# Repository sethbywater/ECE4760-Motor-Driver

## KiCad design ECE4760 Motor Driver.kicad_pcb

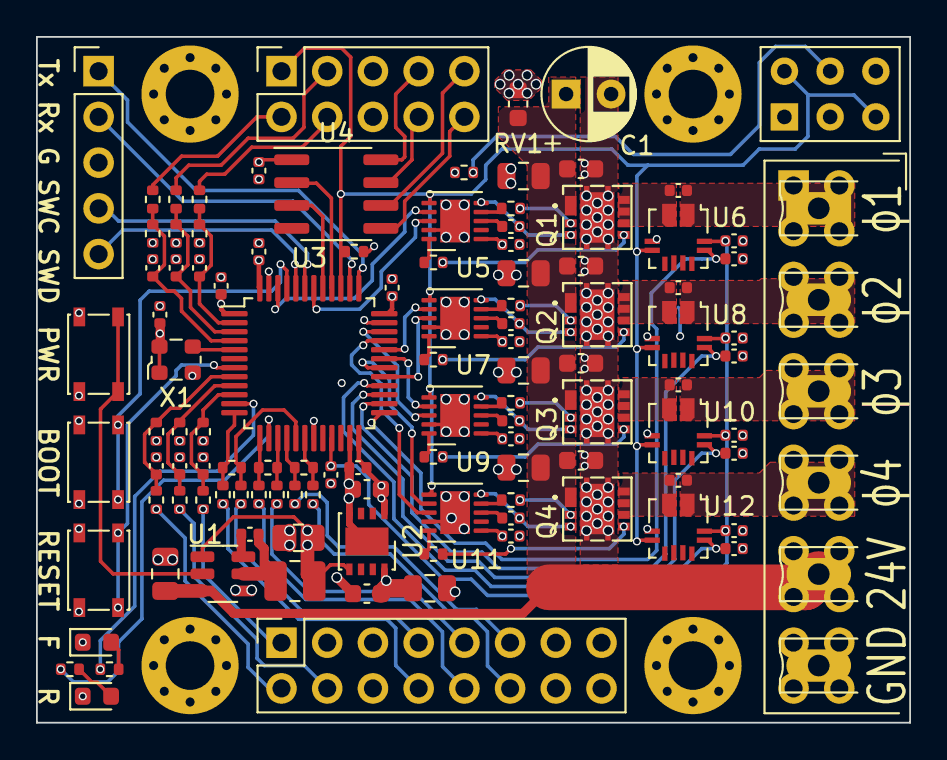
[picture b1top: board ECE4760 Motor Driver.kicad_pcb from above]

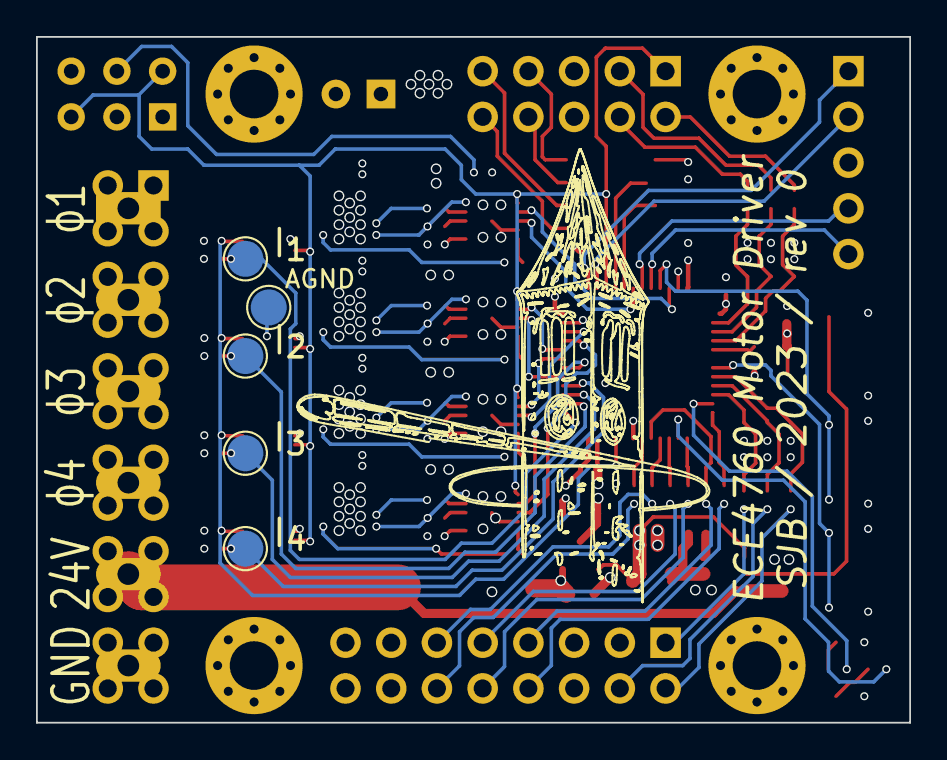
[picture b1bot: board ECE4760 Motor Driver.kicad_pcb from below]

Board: 6 copper layers, 48.5 x 38.1 mm, 120 parts (6 on the bottom side), 94 nets.

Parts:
C1: 22u 100V; CP_Radial_D5.0mm_P2.50mm
C2, C3, C4, C5, C6, C7, C8, C14, C15, C18, C20, C22, C25, C27, C29, C32, C34, C36, C39, C41, C46, C47, C48: 100n; C_0402_1005Metric
C9: 4u7, 50V; C_0805_2012Metric
C10, C11: 22u; C_0805_2012Metric
C12, C13: 4u7; C_0603_1608Metric
C16, C23, C30, C37: 100n, 50V, 0603, X7R; C_0603_1608Metric
C17, C24, C31, C38: 4u7, 50V, 0805, X7R; C_0805_2012Metric
C19, C26, C33, C40: C; C_0402_1005Metric
C21, C28, C35, C42, C43, C44, C45: 1n; C_0402_1005Metric
D1, D2: Green; LED_0603_1608Metric
H1, H2, H3, H4: MountingHole_Pad; MountingHole_2.7mm_M2.5_Pad_Via
J1: Comms; PinHeader_1x05_P2.54mm_Vertical
J2: IO; PinSocket_2x05_P2.54mm_Vertical
J3: IO; PinSocket_2x08_P2.54mm_Vertical
J4: Alternative Motor; PinSocket_2x12_P2.54mm_Vertical
J5: Motor / Power; PhoenixContact_MCV_1,5_6-G-5.08_1x06_P5.08mm_Vertical
L1: 4u7; L_1008_2520Metric
Q1, Q2, Q3, Q4: CSD87333Q3D
R1, R3, R4: 330R; R_0402_1005Metric
R2, R13, R15, R17, R28, R30, R32: 4k7; R_0402_1005Metric
R5, R6, R7, R8, R9, R10, R11, R12: 4R7; R_0402_1005Metric
R14, R16, R18, R29, R31, R33: 100; R_0402_1005Metric
R19, R20, R21, R22, R23, R24, R25, R26, R27: 1k, 1%; R_0402_1005Metric
RV1: 26V 200A; C_0603_1608Metric
SW1: RESET; SW_SPST_PTS810
SW2: BOOT; SW_SPST_PTS810
SW3: POWER; SW_SPST_PTS810
SW4: G12JPC; SW_NKK_G1xJP
TP1, TP2, TP3, TP4, TP5: Sense; TestPoint_Pad_D2.0mm
U1: AP63205WU; TSOT-23-6
U2: AP7361C-33FGE; DFN-8-1EP_3x3mm_P0.65mm_EP1.55x2.4mm
U3: STM32G473CETx; LQFP-48_7x7mm_P0.5mm
U4: THVD1451D; SOIC-8_3.9x4.9mm_P1.27mm
U5, U7, U9, U11: DGD05473FNQ; DFN-10-1EP_3x3mm_P0.5mm_EP1.65x2.38mm
U6, U8, U10, U12: ACS711xEXLT-15AB; Allegro_QFN-12-10-1EP_3x3mm_P0.5mm
X1: 48MHz; Oscillator_SMD_ECS_2520MV-xxx-xx-4Pin_2.5x2.0mm

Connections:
+3V3: C2.2, C3.1, C4.1, C5.1, C6.1, C7.1, C13.1, C14.1, C20.2, C27.2, C34.2, C41.2, U2.1 (OUT), U3.1 (VBAT), U3.21 (VDDA), U3.24 (VDD), U3.36 (VDD), U3.48 (VDD), U4.1 (VCC), U6.10 (VCC), U8.10 (VCC), U10.10 (VCC), U12.10 (VCC), X1.1 (Tri-State), X1.4 (VDD)
+5V: C10.1, C11.1, C12.1, C15.1, C22.1, C29.1, C36.1, J2.5, J3.3, J3.5, J3.13, J3.15, L1.2, R1.2, R2.1, R13.1, R15.1, R17.1, R28.1, R30.1, R32.1, U1.1 (FB), U2.5 (EN), U2.8 (IN), U5.1 (VCC), U7.1 (VCC), U9.1 (VCC), U11.1 (VCC)
/BOOT: SW2.2, U3.45 (PB8)
/CLK: U3.40 (SPI1_SCK), U4.2 (R)
/DATA: U3.41 (SPI1_MISO), U4.3 (D)
/ENC_A+: R22.2, R23.2, U3.15 (COMP2_INP)
/ENC_A-: R23.1, R24.2, U3.13 (COMP2_INM)
/ENC_B+: R25.2, R26.2, U3.16 (COMP4_INP)
/ENC_B-: R26.1, R27.2, U3.18 (COMP4_INM)
/ENC_I+: R19.2, R20.2, U3.17 (COMP1_INP)
/ENC_I-: R20.1, R21.2, U3.12 (COMP1_INM)
/HALL_A: C45.1, R17.2, R18.2, U3.8 (TIM2_CH1)
/HALL_B: C43.1, R13.2, R14.2, U3.9 (TIM2_CH2)
/HALL_C: C44.1, R15.2, R16.2, U3.10 (TIM2_CH3)
/LED_1: R3.1, U3.11 (PA3)
/LED_2: R4.1, U3.14 (PA6)
/LIM_H: C48.1, R32.2, R33.2, U3.4 (PC15)
/LIM_L: C46.1, R28.2, R29.2, U3.2 (PC13)
/LIM_R: C47.1, R30.2, R31.2, U3.3 (PC14)
/OSC_IN: U3.5 (RCC_OSC_IN), X1.3 (OUT)
/PH1_HI: U3.46 (TIM8_CH3), U5.7 (HIN)
/PH1_LO: U3.42 (TIM8_CH3N), U5.8 (LIN)
/PH1_SENSE: C21.2, TP2.1, U3.25 (OPAMP4_VINP), U6.9 (VIOUT)
/PH2_HI: U3.32 (TIM1_CH3), U7.7 (HIN)
/PH2_LO: U3.29 (TIM1_CH3N), U7.8 (LIN)
/PH2_SENSE: C28.2, TP3.1, U3.26 (OPAMP6_VINP), U8.9 (VIOUT)
/PH3_HI: U3.31 (TIM1_CH2), U9.7 (HIN)
/PH3_LO: U3.34 (TIM1_CH2N), U9.8 (LIN)
/PH3_SENSE: C35.2, TP4.1, U3.27 (OPAMP3_VINP), U10.9 (VIOUT)
/PH4_HI: U3.30 (TIM1_CH1), U11.7 (HIN)
/PH4_LO: U3.33 (TIM1_CH1N), U11.8 (LIN)
/PH4_SENSE: C42.2, TP5.1, U3.28 (OPAMP2_VINP), U12.9 (VIOUT)
/SWCLK: J1.2, U3.38 (SYS_JTCK-SWCLK)
/SWDIO: J1.1, U3.37 (SYS_JTMS-SWDIO)
/UART_RX: J1.5, U3.44 (USART1_RX)
/UART_TX: J1.4, U3.43 (USART1_TX)
/~RST: SW1.2, U3.7 (RCC_MCO)
CLK+: J2.7, U4.8 (A)
CLK-: J2.8, U4.7 (B)
DATA+: J2.10, U4.5 (Y)
DATA-: J2.9, U4.6 (Z)
Enc_A_In+: J3.9, R22.1
Enc_A_In-: J3.10, R24.1
Enc_B_In+: J3.11, R25.1
Enc_B_In-: J3.12, R27.1
Enc_I_In+: J3.7, R19.1
Enc_I_In-: J3.8, R21.1
Fault_Enable: J2.1, R2.2, SW4.3, SW4.6 (K), U3.39 (PA15), U5.6 (EN), U6.4 (~FAULT), U7.6 (EN), U8.4 (~FAULT), U9.6 (EN), U10.4 (~FAULT), U11.6 (EN), U12.4 (~FAULT)
GND: C1.2, C2.1, C3.2, C4.2, C5.2, C6.2, C7.2, C9.2, C10.2, C11.2, C12.2, C13.2, C14.2, C15.2, C16.2, C17.2, C20.1, C21.1, C22.2, C23.2, C24.2, C27.1, C28.1, C29.2, C30.2, C31.2, C34.1, C35.1, C36.2, C37.2, C38.2, C41.1, C42.1, C43.2, C44.2, C45.2, C46.2, C47.2, C48.2, D1.1 (K), D2.1 (K), H1.1, H2.1, H3.1, H4.1, J1.3, J2.6, J3.6, J3.14, J3.16, J4.21, J4.22, J4.23, J4.24, J5.6, Q1.9 (GND), Q1.10 (GND), Q1.11 (GND), Q1.12 (GND), Q1.13 (GND), Q2.9 (GND), Q2.10 (GND), Q2.11 (GND), Q2.12 (GND), Q2.13 (GND), Q3.9 (GND), Q3.10 (GND), Q3.11 (GND), Q3.12 (GND), Q3.13 (GND), Q4.9 (GND), Q4.10 (GND), Q4.11 (GND), Q4.12 (GND), Q4.13 (GND), RV1.2, SW1.1, SW2.1, SW3.1, SW4.2 (COM), TP1.1, U1.4 (GND), U2.4 (GND), U2.9 (GND), U3.19 (VSSA), U3.23 (VSS), U3.35 (VSS), U3.47 (VSS), U4.4 (GND), U5.9 (COM), U5.11 (EP), U6.3 (GND), U7.9 (COM), U7.11 (EP), U8.3 (GND), U9.9 (COM), U9.11 (EP), U10.3 (GND), U11.9 (COM), U11.11 (EP), U12.3 (GND), X1.2 (GND)
Hall_A_In: J3.2, R18.1
Hall_B_In: J3.4, R14.1
Hall_C_In: J3.1, R16.1
Lim_H_In: J2.2, R33.1
Lim_L_In: J2.4, R29.1
Lim_R_In: J2.3, R31.1
unnamed: D1.2 (A), R4.2
unnamed: D2.2 (A), R3.2
unnamed: Q1.5 (BG), R6.2
unnamed: Q1.3 (TG), R5.1
unnamed: C18.2, Q1.4 (TGR), U5.5 (VS)
unnamed: Q2.5 (BG), R8.2
unnamed: Q2.3 (TG), R7.1
unnamed: C25.2, Q2.4 (TGR), U7.5 (VS)
unnamed: Q3.5 (BG), R10.2
unnamed: Q3.3 (TG), R9.1
unnamed: C32.2, Q3.4 (TGR), U9.5 (VS)
unnamed: Q4.5 (BG), R12.2
unnamed: Q4.3 (TG), R11.1
unnamed: C39.2, Q4.4 (TGR), U11.5 (VS)
unnamed: R1.1, SW4.5 (A)
unnamed: C8.1, U1.6 (BST)
unnamed: SW3.2, U1.2 (EN)
unnamed: C8.2, L1.1, U1.5 (SW)
unnamed: R5.2, U5.4 (HO)
unnamed: R6.1, U5.10 (LO)
unnamed: C18.1, U5.3 (VB)
unnamed: C19.1, Q1.6 (SW), Q1.7 (SW), Q1.8 (SW), U6.2 (IP-)
unnamed: R7.2, U7.4 (HO)
unnamed: R8.1, U7.10 (LO)
unnamed: C25.1, U7.3 (VB)
unnamed: C26.1, Q2.6 (SW), Q2.7 (SW), Q2.8 (SW), U8.2 (IP-)
unnamed: R9.2, U9.4 (HO)
unnamed: R10.1, U9.10 (LO)
unnamed: C32.1, U9.3 (VB)
unnamed: C33.1, Q3.6 (SW), Q3.7 (SW), Q3.8 (SW), U10.2 (IP-)
unnamed: R11.2, U11.4 (HO)
unnamed: R12.1, U11.10 (LO)
unnamed: C39.1, U11.3 (VB)
unnamed: C40.1, Q4.6 (SW), Q4.7 (SW), Q4.8 (SW), U12.2 (IP-)
PH1: C19.2, J4.1, J4.2, J4.3, J4.4, J5.1, U6.1 (IP+)
PH2: C26.2, J4.5, J4.6, J4.7, J4.8, J5.2, U8.1 (IP+)
PH3: C33.2, J4.9, J4.10, J4.11, J4.12, J5.3, U10.1 (IP+)
PH4: C40.2, J4.13, J4.14, J4.15, J4.16, J5.4, U12.1 (IP+)
Vdrive: C1.1, C9.1, C16.1, C17.1, C23.1, C24.1, C30.1, C31.1, C37.1, C38.1, J4.17, J4.18, J4.19, J4.20, J5.5, Q1.1 (VIN), Q2.1 (VIN), Q3.1 (VIN), Q4.1 (VIN), RV1.1, U1.3 (IN)

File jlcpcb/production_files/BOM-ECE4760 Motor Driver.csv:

Comment,Designator,Footprint,LCSC
4k7,"R13,R15,R17,R2,R28,R30,R32",R_0402_1005Metric,C105870
330R,"R1,R3,R4",R_0402_1005Metric,C105875
100,"R14,R16,R18,R29,R31,R33",R_0402_1005Metric,C106233
Green,"D1,D2",LED_0603_1608Metric,C125101
4R7,"R10,R11,R12,R5,R6,R7,R8,R9",R_0402_1005Metric,C137862
ACS711xEXLT-15AB,"U10,U12,U6,U8",Allegro_QFN-12-10-1EP_3x3mm_P0.5mm,C150824
AP7361C-33FGE,U2,DFN-8-1EP_3x3mm_P0.65mm_EP1.55x2.4mm,C151007
"100n, 50V, 0603, X7R","C16,C23,C30,C37",C_0603_1608Metric,C161117
AP63205WU,U1,TSOT-23-6,C2071056
RESET,"SW1,SW2,SW3",SW_SPST_PTS810,C221896
"1k, 1%","R19,R20,R21,R22,R23,R24,R25,R26,R27",R_0402_1005Metric,C242161
26V 200A,RV1,C_0603_1608Metric,C2655584
THVD1451D,U4,SOIC-8_3.9x4.9mm_P1.27mm,C2671319
DGD05473FNQ,"U11,U5,U7,U9",DFN-10-1EP_3x3mm_P0.5mm_EP1.65x2.38mm,C2677131
1n,"C21,C28,C35,C42,C43,C44,C45",C_0402_1005Metric,C277522
48MHz,X1,Oscillator_SMD_ECS_2520MV-xxx-xx-4Pin_2.5x2.0mm,C390534
4u7,"C12,C13,C17,C24,C31,C38,C9",C_0603_1608Metric,C437557
100n,"C14,C15,C18,C2,C20,C22,C25,C27,C29,C3,C32,C34,C36,C39,C4,C41,C46,C47,C48,C5,C6,C7,C8",C_0402_1005Metric,C71629
STM32G473CETx,U3,LQFP-48_7x7mm_P0.5mm,C730111
4u7,L1,L_1008_2520Metric,C82314
22u,"C10,C11",C_0805_2012Metric,C86816
CSD87333Q3D,"Q1,Q2,Q3,Q4",CSD87333Q3D,C90396
IO,J2,PinSocket_2x05_P2.54mm_Vertical,
22u 100V,C1,CP_Radial_D5.0mm_P2.50mm,
C,C33,C_0402_1005Metric,
Comms,J1,PinHeader_1x05_P2.54mm_Vertical,
C,C19,C_0402_1005Metric,
IO,J3,PinSocket_2x08_P2.54mm_Vertical,
G12JPC,SW4,SW_NKK_G1xJP,
Alternative Motor,J4,PinSocket_2x12_P2.54mm_Vertical,
C,C40,C_0402_1005Metric,
C,C26,C_0402_1005Metric,
Motor / Power,J5,"PhoenixContact_MCV_1,5_6-G-5.08_1x06_P5.08mm_Vertical",

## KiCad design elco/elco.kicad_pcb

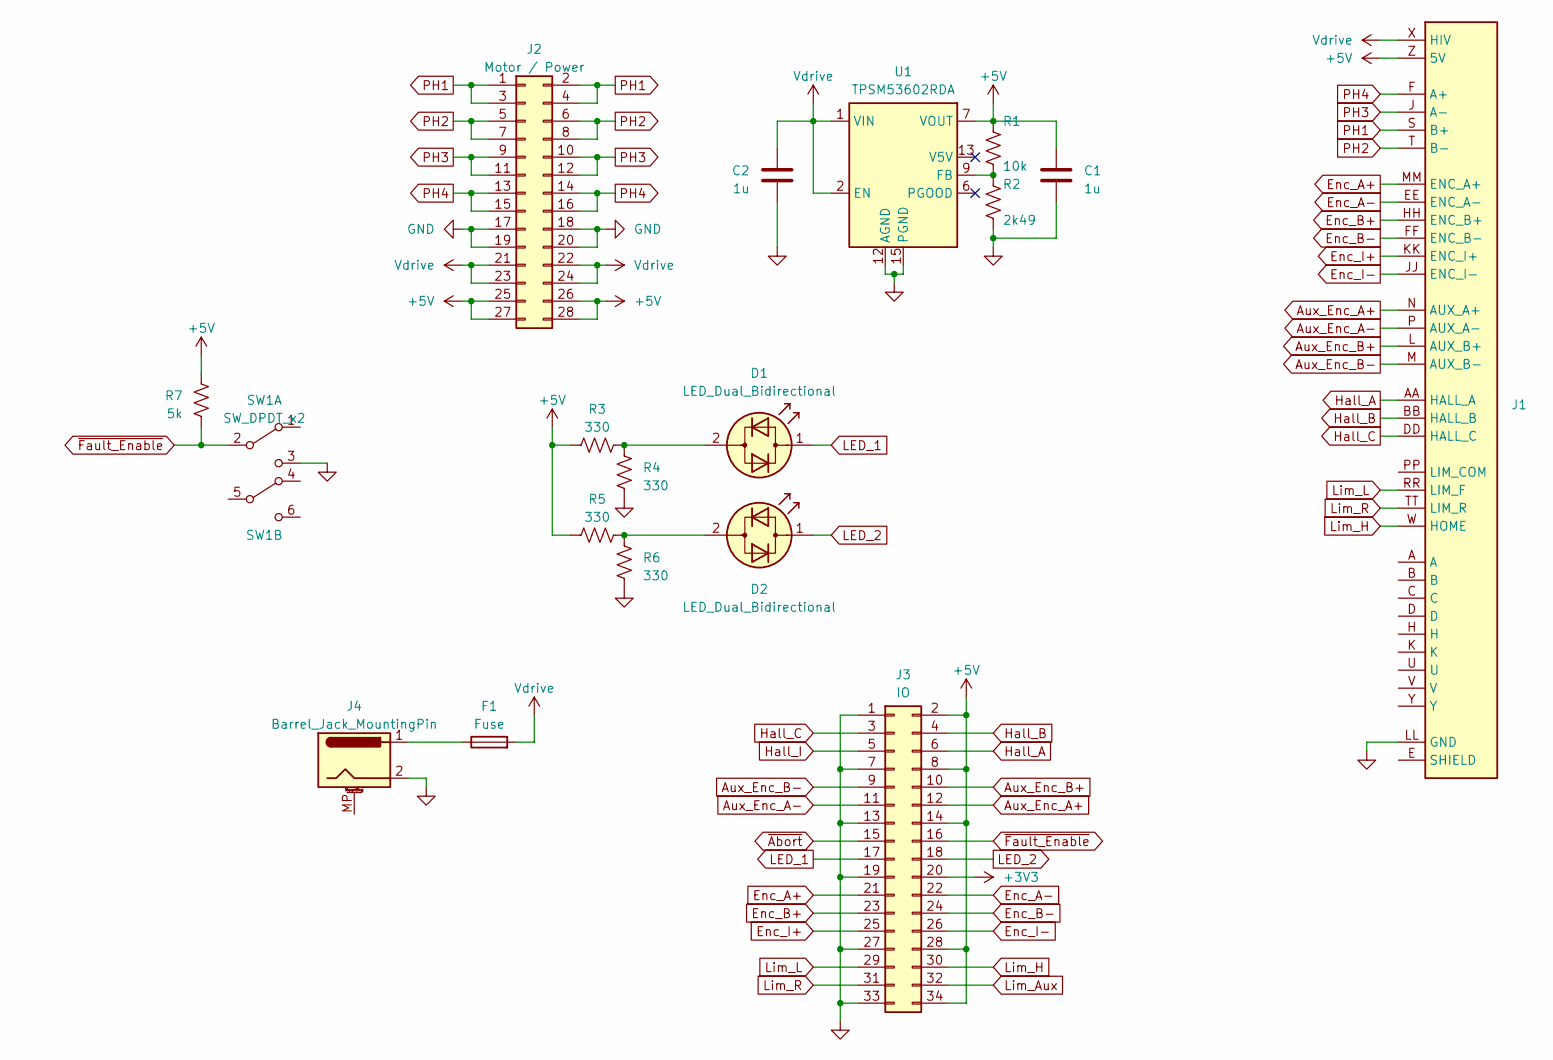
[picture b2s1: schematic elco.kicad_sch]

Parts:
C1, C2: 1u; C_0805_2012Metric
D1, D2: LED_Dual_Bidirectional; LED_D5.0mm
F1: Fuse; Fuseholder_Clip-5x20mm_Bel_FC-203-22_Lateral_P17.80x5.00mm_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
J1: ELCO
J2: Motor / Power; PinHeader_2x14_P2.54mm_Vertical
J3: IO; PinHeader_2x17_P2.54mm_Vertical
J4: Barrel_Jack_MountingPin; BarrelJack_CUI_PJ-063AH_Horizontal
R1: 10k; R_0805_2012Metric
R2: 2k49; R_0805_2012Metric
R3, R4, R5, R6: 330; R_0805_2012Metric
R7: 5k; R_0805_2012Metric
SW1: SW_DPDT_x2; SW_NKK_G1xJP
U1: TPSM53602RDA; Texas_B3QFN-14-1EP_5x5.5mm_P0.65mm_ThermalVia

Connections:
+3V3: J3.20
+5V: C1.1, J1.NN (5V), J1.Z (5V), J2.25, J2.26, J2.27, J2.28, J3.2, J3.8, J3.14, J3.28, J3.34, R1.1, R3.1, R5.2, R7.1, U1.7 (VOUT), U1.8 (VOUT)
Aux_Enc_A+: J1.N (AUX_A+), J3.12
Aux_Enc_A-: J1.P (AUX_A-), J3.11
Aux_Enc_B+: J1.L (AUX_B+), J3.10
Aux_Enc_B-: J1.M (AUX_B-), J3.9
Enc_A+: J1.MM (ENC_A+), J3.21
Enc_A-: J1.EE (ENC_A-), J3.22
Enc_B+: J1.HH (ENC_B+), J3.23
Enc_B-: J1.FF (ENC_B-), J3.24
Enc_I+: J1.KK (ENC_I+), J3.25
Enc_I-: J1.JJ (ENC_I-), J3.26
GND: C1.2, C2.2, J1.LL (GND), J2.17, J2.18, J2.19, J2.20, J3.1, J3.7, J3.13, J3.19, J3.27, J3.33, J4.2, R2.2, R4.1, R6.2, SW1.3 (C), U1.3 (PGND), U1.10 (PGND), U1.11 (PGND), U1.12 (AGND), U1.15 (PGND)
Hall_A: J1.AA (HALL_A), J3.6
Hall_B: J1.BB (HALL_B), J3.4
Hall_C: J1.DD (HALL_C), J3.3
Hall_I: J3.5
LED_1: D1.1 (KA), J3.17
LED_2: D2.1 (KA), J3.18
Lim_Aux: J3.32
Lim_H: J1.W (HOME), J3.30
Lim_L: J1.RR (LIM_F), J3.29
Lim_R: J1.TT (LIM_R), J3.31
unnamed: D1.2 (AK), R3.2, R4.2
unnamed: D2.2 (AK), R5.1, R6.1
unnamed: F1.1, J4.1
unnamed: J1.PP (LIM_COM), J1.SS (LIM_COM)
unnamed: J1.CC (SHIELD), J1.E (SHIELD), J1.R (SHIELD)
unnamed: R1.2, R2.1, U1.9 (FB)
PH1: J1.S (B+), J2.1, J2.2, J2.3, J2.4
PH2: J1.T (B-), J2.5, J2.6, J2.7, J2.8
PH3: J1.J (A-), J2.9, J2.10, J2.11, J2.12
PH4: J1.F (A+), J2.13, J2.14, J2.15, J2.16
Vdrive: C2.1, F1.2, J1.X (HIV), J2.21, J2.22, J2.23, J2.24, U1.1 (VIN), U1.2 (EN), U1.14 (VIN)
~Abort: J3.15
~Fault_Enable: J3.16, R7.2, SW1.2 (B)

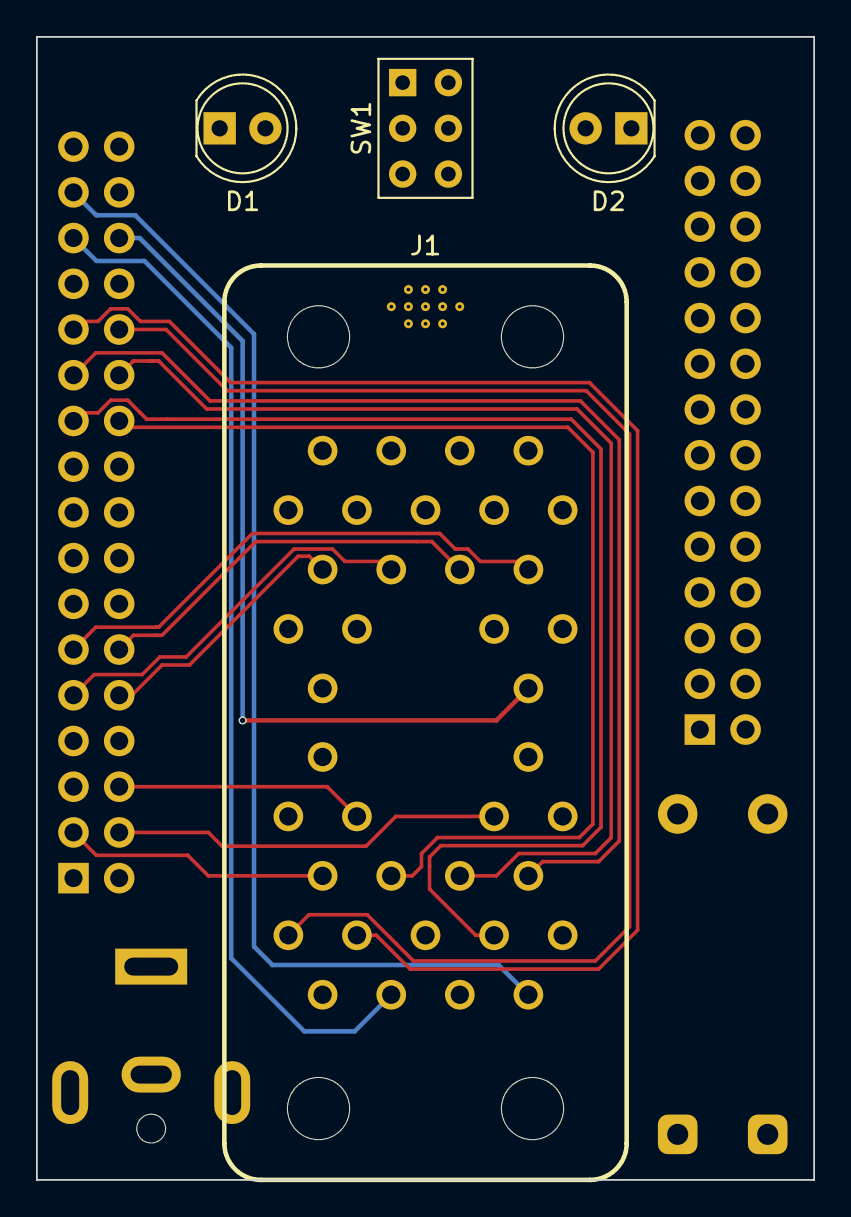
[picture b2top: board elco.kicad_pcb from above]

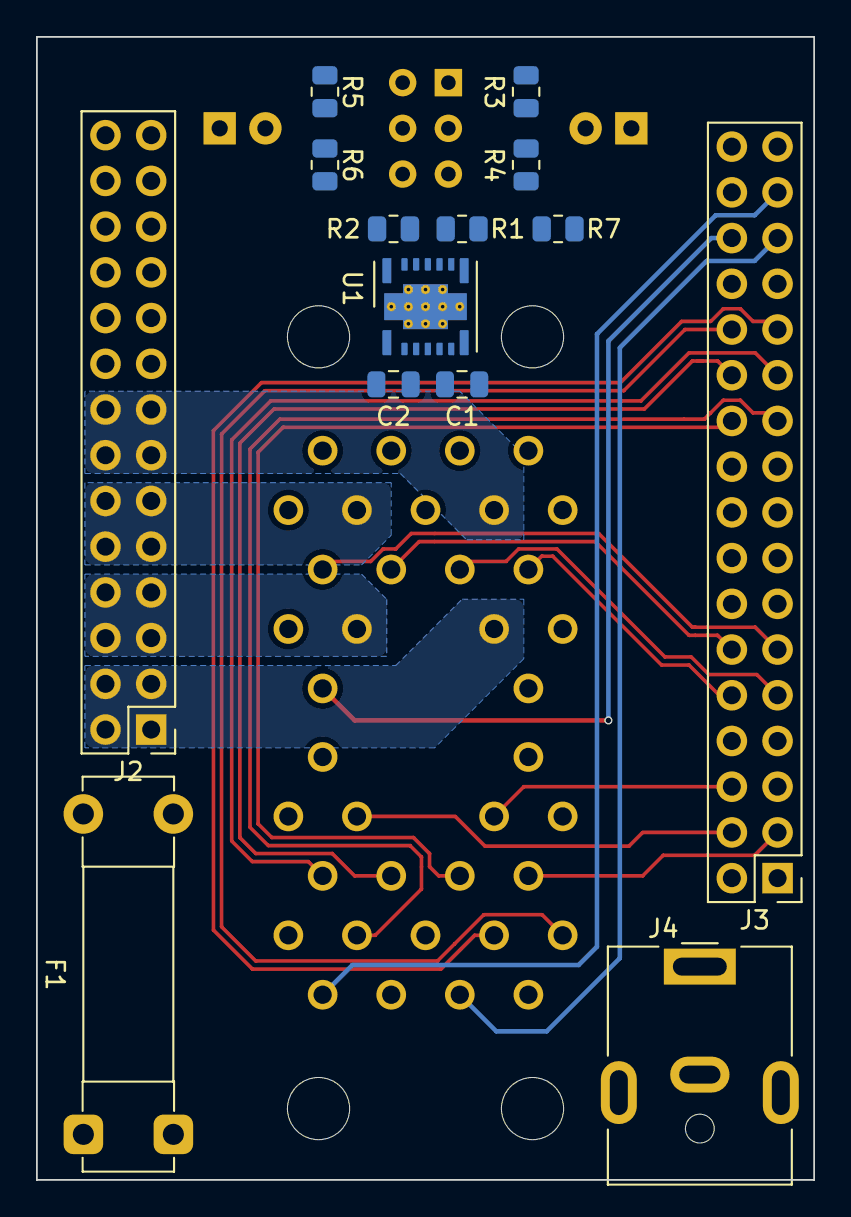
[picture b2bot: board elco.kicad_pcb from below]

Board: 4 copper layers, 43.2 x 63.5 mm, 18 parts (14 on the bottom side), 32 nets.

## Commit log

2023-10-30 Create repository
2023-11-01 Updating cap specs
2023-11-02 Elco board
2023-11-07 ELCO routing
2023-11-08 Getting ready for fab
2023-11-08 Play around with switching to RP2040
2023-11-08 3D models
2023-11-08 Start effort to move components to single side
2023-11-10 Single-sided component placement
2023-11-13 Updated routing
2023-11-15 Power supply and remove USB
2023-11-15 Limit switch inputs and silkscreen
2023-11-16 Update hall sensor circuit for 5V-tolerant pins
2023-11-20 FOC math refrence
2023-11-20 Ready for design review
2023-11-28 Tweaking pin assignments
2023-12-01 Change MCU package and MOSFETs
2023-12-15 Boards ordered!
2023-12-22 Vacation
